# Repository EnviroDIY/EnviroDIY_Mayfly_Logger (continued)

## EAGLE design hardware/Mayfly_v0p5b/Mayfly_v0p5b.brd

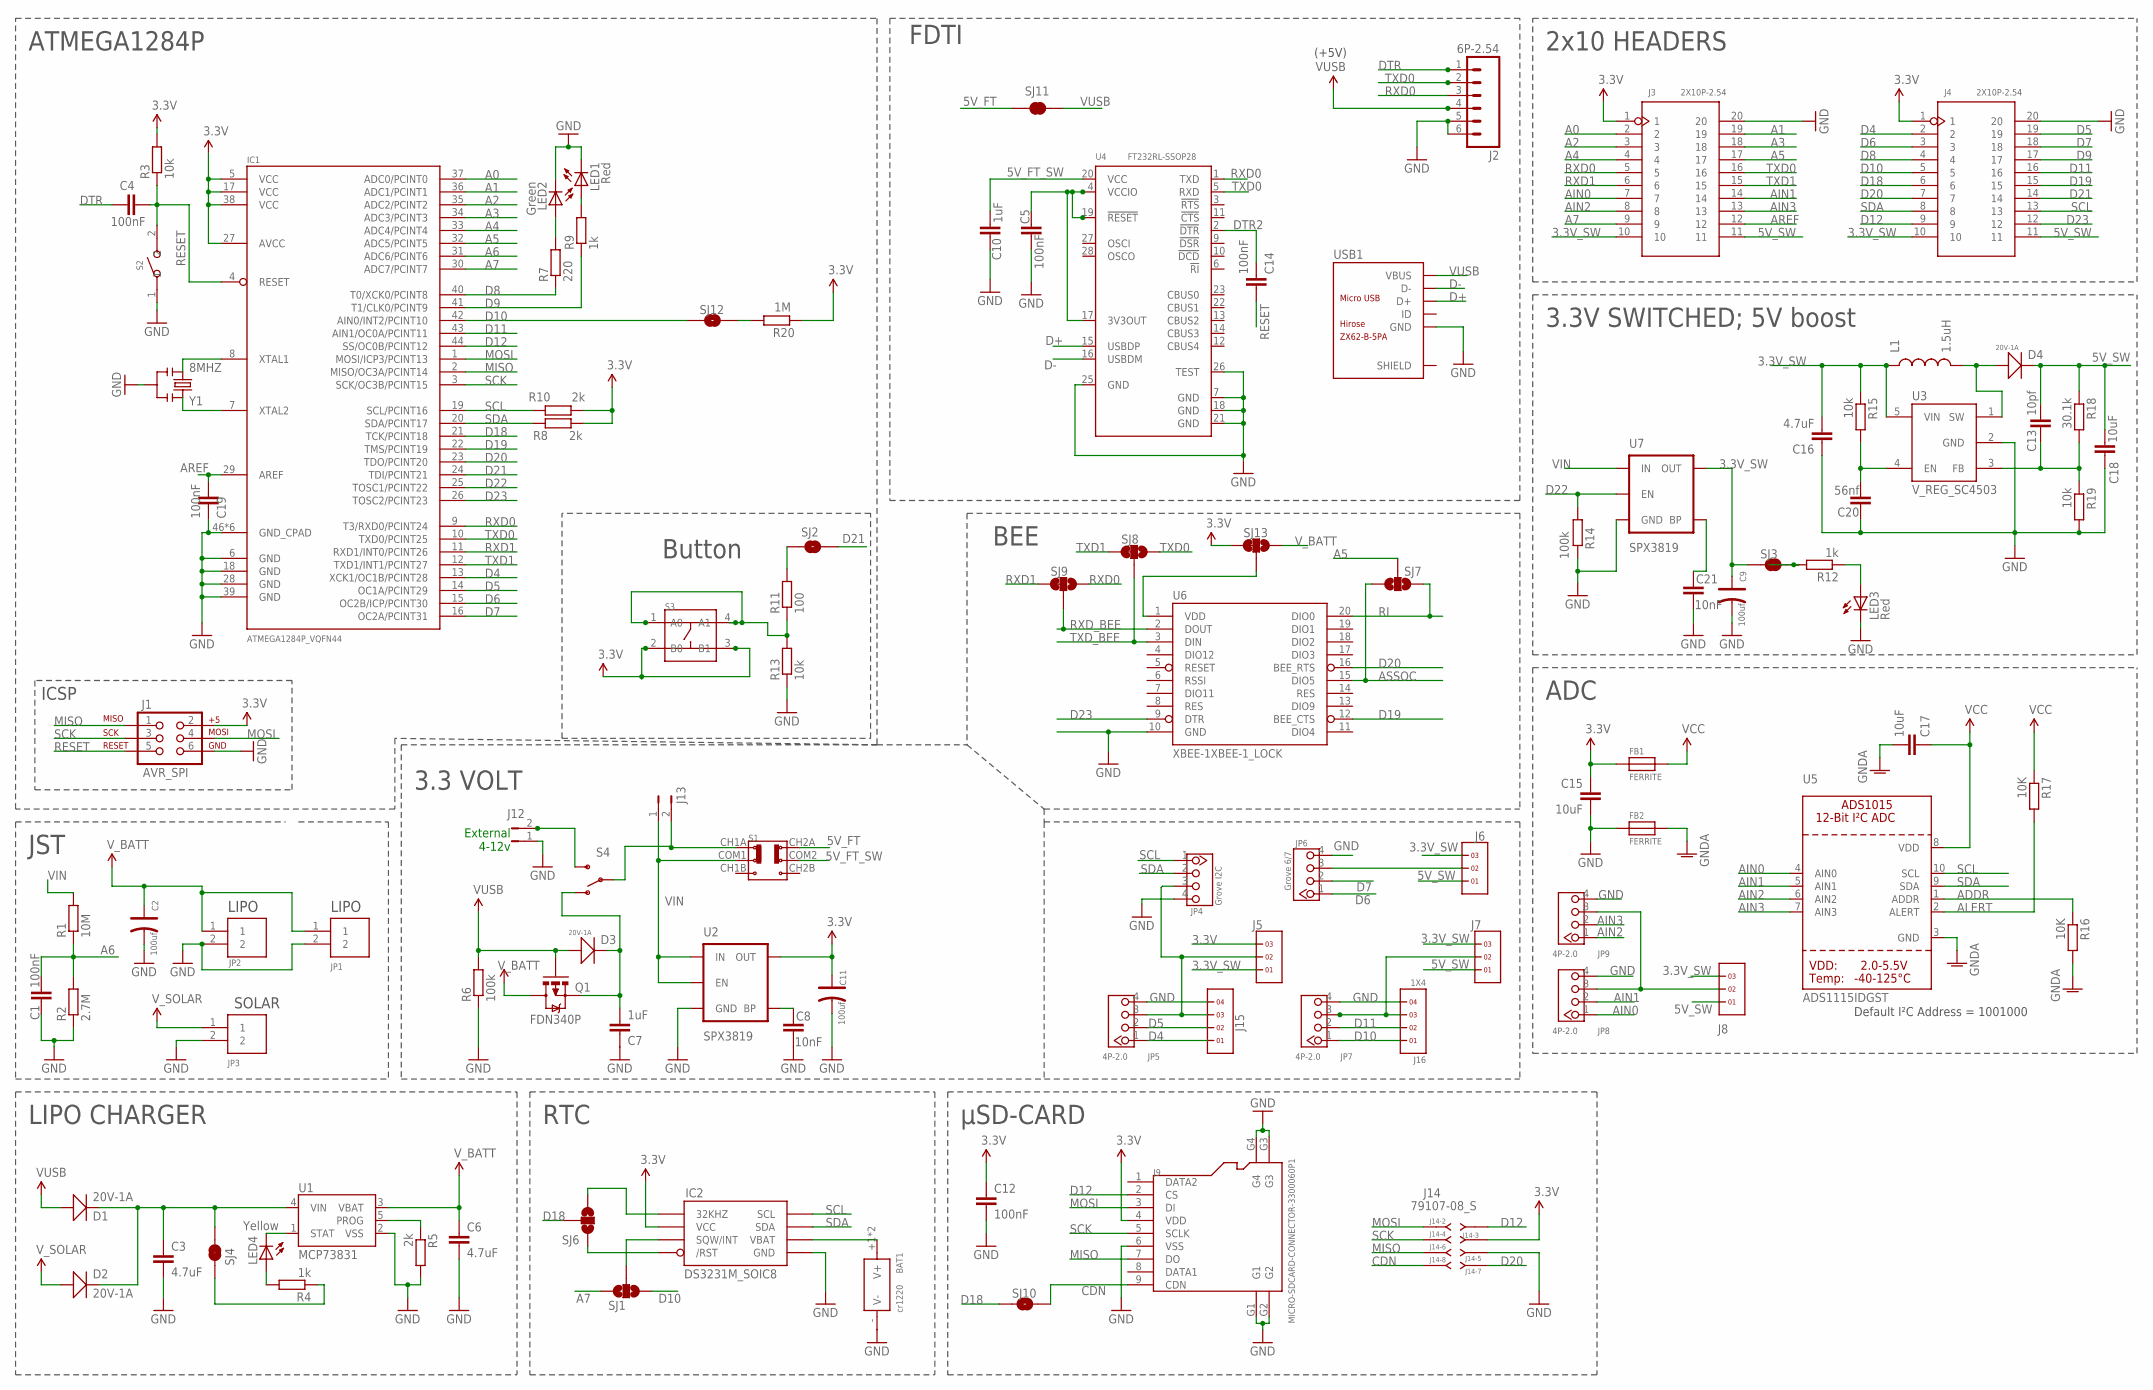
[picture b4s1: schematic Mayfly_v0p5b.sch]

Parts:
BAT1: cr1220; BAT2P-13.5-CR1220
C1, C4, C5, C12, C14, C19: 100nF; C0603
C2, C9, C11: 100uf; AVX-B
C3, C6: 4.7uF; C0603
C7, C10: 1uF; C0603
C8, C21: 10nF; C0603
C13: 10pf; 0603-CAP
C15, C17: 10uF; C0603
C16: 4.7uF; 0805
C18: 10uF; 0805
C20: 56nf; 0603-CAP
D1, D2, D3, D4: 20V-1A; SOD-123
FB1, FB2: FERRITE; 0805
IC1: ATMEGA1284P_VQFN44; VQFN44
IC2: DS3231M_SOIC8; SO8
J1: AVR_SPI; 2X3-NS
J2: 6P-2.54; 1X06_FEMALE_LOCK.010
J3, J4: 2X10P-2.54; H2X10-2.54
J5, J6, J7, J8: 1X3
J9: MICRO-SDCARD-CONNECTOR-3300060P1; 9P-SMD-W-RING
J12, J13: JUMPER-PTH-2-NO; PTH-JUMPER-2-NO_NO_SILK
J14: 79107-08_S; 79107-08
J15, J16: 1X4
JP1, JP2, JP3: JST_EPH_2PIN; JST_EPH_B2B-PH-K-S
JP4: Grove I2C; HW4-2.0
JP5, JP7, JP8, JP9: 4P-2.0; HW4-2.0
JP6: Grove 6/7; HW4-2.0
L1: 1.5uH; VLF4012A
LED1, LED3: Red; LED-0603
LED2: Green; LED-0603
LED4: Yellow; LED-0603
Q1: FDN340P; SOT23-S-PADS
R1: 10M; R0603
R2: 2.7M; R0603
R3, R13, R15, R19: 10k; R0603
R4, R9, R12: 1k; R0603
R5, R8, R10: 2k; R0603
R6, R14: 100k; R0603
R7: 220; R0603
R11: 100; R0603
R16, R17: 10K; R0603
R18: 30.1k; R0603
R20: 1M; R0603
S1: SWITCH-2CH-6P-3010010P1; 6P-2CH-2.54-9.1X3.5X3.2+2H
S2: SMD-BUTTON(2P-6.0X3.0X2.5MM)-DHT-1163S; SW2-4.0-6.0X3.0X2.5MM
S3: SMD-SWITCH-TACTILE-SPST-NO(4P-D6.0MM); SW4-SMD-6.0X6.0X5.0MM
S4: SWITCH-SPDT-SMD-A; SWITCH-SPST-SMD-A
SJ1, SJ6, SJ7: SOLDERJUMPER_2WAYT; SJ_2
SJ2, SJ3, SJ10, SJ12: SOLDERJUMPERNO; SJ_2S-NO
SJ4: SOLDERJUMPER_NC; SJ_2S_NC
SJ8, SJ9, SJ13: SJ_3WAY_12SHORT
SJ11: JUMPER-PAD-2-NC_BY_TRACENO_SILK; PAD-JUMPER-2-NC_BY_TRACE_NO_SILK
U1: MCP73831; SOT23-5
U2, U7: SPX3819; SOT23-5
U3: V_REG_SC4503; SOT23-5
U4: FT232RL-SSOP28; SSOP28-0.65-10.2X5.2MM
U5: ADS1115IDGST; MSOP10
U6: XBEE-1XBEE-1_LOCK; XBEE-1_LOCK
USB1: ZX62-B-5PA; MICRO-USB5+6P-SMD-0.65-AB
Y1: 8MHZ; X3-SMD-3.6X1.3X0.8MM

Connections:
1.8V: D2.+, JP3.1
3.3V: C11.+, C12.2, C15.1, FB1.1, IC1.5 (VCC), IC1.17 (VCC), IC1.27 (AVCC), IC1.38 (VCC), IC2.2 (VCC), J1.2, J3.1, J4.1, J5.3, J9.4 (VDD), J14.3, R3.2, R8.1, R10.2, R20.2, S3.2 (B0), S3.3 (B1), SJ13.1, U2.5 (OUT)
3.3V_SW: C9.+, C16.2, J3.10, J4.10, J5.1, J6.3, J7.3, J8.3, L1.P$1 (1), R15.1, SJ3.1, U3.5 (VIN), U7.5 (OUT)
5V_FT: S1.CH2A, SJ11.1
5V_FT_SW: C10.2, S1.COM2, U4.20 (VCC)
5V_SW: C13.2, C18.1, D4.-, J3.11, J4.11, J6.1, J7.1, J8.1, R18.1
A0: IC1.37 (ADC0/PCINT0), J3.2
A1: IC1.36 (ADC1/PCINT1), J3.19
A2: IC1.35 (ADC2/PCINT2), J3.3
A3: IC1.34 (ADC3/PCINT3), J3.18
A4: IC1.33 (ADC4/PCINT4), J3.4
A5: IC1.32 (ADC5/PCINT5), J3.17, SJ7.2
A6: C1.2, IC1.31 (ADC6/PCINT6), R1.1, R2.2
A7: IC1.30 (ADC7/PCINT7), J3.9, SJ1.3
ADDR: R16.1, U5.1 (ADDR)
AIN0: J3.7, JP8.1, U5.4 (AIN0)
AIN1: J3.14, JP8.2, U5.5 (AIN1)
AIN2: J3.8, JP9.1, U5.6 (AIN2)
AIN3: J3.13, JP9.2, U5.7 (AIN3)
ALERT: R17.2, U5.2 (ALERT)
AREF: C19.2, IC1.29 (AREF), J3.12
ASSOC: SJ7.3, U6.15 (DIO5)
C: IC1.8 (XTAL1), Y1.1
CDN: J9.9 (CDN), J14.8, SJ10.2
C_N: IC1.7 (XTAL2), Y1.3
D4: IC1.13 (XCK1/OC1B/PCINT28), J4.2, J15.1, JP5.1
D5: IC1.14 (OC1A/PCINT29), J4.19, J15.2, JP5.2
D6: IC1.15 (OC2B/ICP/PCINT30), J4.3, JP6.1
D7: IC1.16 (OC2A/PCINT31), J4.18, JP6.2
D8: IC1.40 (T0/XCK0/PCINT8), J4.4, R7.1
D9: IC1.41 (T1/CLK0/PCINT9), J4.17, R9.1
D10: IC1.42 (AIN0/INT2/PCINT10), J4.5, J16.1, JP7.1, SJ1.1, SJ12.1
D11: IC1.43 (AIN1/OC0A/PCINT11), J4.16, J16.2, JP7.2
D12: IC1.44 (SS/OC0B/PCINT12), J4.9, J9.2 (CS), J14.1
D18: IC1.21 (TCK/PCINT18), J4.6, SJ6.2, SJ10.1
D19: IC1.22 (TMS/PCINT19), J4.15, U6.12 (BEE_CTS)
D20: IC1.23 (TDO/PCINT20), J4.7, J14.7, U6.16 (BEE_RTS)
D21: IC1.24 (TDI/PCINT21), J4.14, SJ2.2
D22: IC1.25 (TOSC1/PCINT22), R14.2, U7.3 (EN)
D23: IC1.26 (TOSC2/PCINT23), J4.12, U6.9 (DTR)
D+: U4.15 (USBDP), USB1.3 (D+)
D-: U4.16 (USBDM), USB1.2 (D-)
DTR: C4.1, J2.1
DTR2: C14.2, U4.2 (!DTR)
GND: BAT1.- (V-), C1.1, C2.-, C3.2, C5.1, C6.2, C7.1, C8.1, C9.-, C10.1, C11.-, C12.1, C15.2, C16.1, C18.2, C19.1, C20.1, C21.1, FB2.1, IC1.6 (GND), IC1.18 (GND), IC1.28 (GND), IC1.39 (GND), IC1.46 (GND_CPAD), IC1.GND@0 (GND_CPAD), IC1.GND@1 (GND_CPAD), IC1.GND@2 (GND_CPAD), IC1.GND@3 (GND_CPAD), IC1.GND@4 (GND_CPAD), IC2.5 (GND), J1.6, J2.5, J2.6, J3.20, J4.20, J9.6 (VSS), J9.G1, J9.G2, J9.G3, J9.G4, J12.1, J14.5, J15.4, J16.4, JP1.2, JP2.2, JP3.2, JP4.4, JP5.4, JP6.4, JP7.4, JP8.4, JP9.4, LED1.C, LED2.C, LED3.C, R2.1, R5.2, R6.1, R13.1, R14.1, R19.2, S2.1, U1.2 (VSS), U2.2 (GND), U3.2 (GND), U4.7 (GND), U4.18 (GND), U4.21 (GND), U4.25 (GND), U4.26 (TEST), U6.10 (GND), U7.2 (GND), USB1.5 (GND), Y1.2
GNDA: C17.2, FB2.2, R16.2, U5.3 (GND)
LIPO_STAT: LED4.C, U1.1 (STAT)
MISO: IC1.2 (MISO/OC3A/PCINT14), J1.1, J9.7 (DO), J14.6
MOSI: IC1.1 (MOSI/ICP3/PCINT13), J1.4, J9.3 (DI), J14.2
unnamed: R20.1, SJ12.2
unnamed: C8.2, U2.4 (BP)
unnamed: R12.2, SJ3.2
unnamed: LED3.A, R12.1
unnamed: R11.1, R13.2, S3.1 (A0), S3.4 (A1)
unnamed: J8.2, JP8.3, JP9.3
unnamed: C5.2, U4.4 (VCCIO), U4.17 (3V3OUT), U4.19 (!RESET)
unnamed: D4.+, L1.P$2 (2), U3.1 (SW)
unnamed: SJ13.2, U6.1 (VDD)
unnamed: IC2.3 (SQW/INT), SJ1.2
unnamed: C7.2, D3.-, Q1.2 (S), S4.1 (O)
unnamed: LED4.A, R4.2
unnamed: R5.1, U1.5 (PROG)
unnamed: C3.1, D1.-, D2.-, SJ4.2, U1.4 (VIN)
unnamed: R4.1, SJ4.1
unnamed: J5.2, J15.3, JP4.3, JP5.3
unnamed: R11.2, SJ2.1
unnamed: J6.2, JP6.3
unnamed: J12.2, S4.3 (S)
unnamed: C21.2, U7.4 (BP)
unnamed: C13.1, R18.2, R19.1, U3.3 (FB)
unnamed: J7.2, J16.3, JP7.3
unnamed: J13.2, S1.CH1A, S4.2
unnamed: C20.2, R15.2, U3.4 (EN)
unnamed: LED1.A, R9.2
unnamed: BAT1.+1 (V+), BAT1.+2 (V+), IC2.6 (VBAT)
unnamed: LED2.A, R7.2
RESET: C4.2, C14.1, IC1.4 (RESET), J1.5, R3.1, S2.2
RI: SJ7.1, U6.20 (DIO0)
RTC_32KHZ: IC2.1 (32KHZ), SJ6.1
RTC_RST: IC2.4 (/RST), SJ6.3
RXD0: IC1.9 (T3/RXD0/PCINT24), J2.3, J3.5, SJ9.3, U4.1 (TXD)
RXD1: IC1.11 (RXD1/INT0/PCINT26), J3.6, SJ9.1
RXD_BEE: SJ9.2, U6.2 (DOUT)
SCK: IC1.3 (SCK/OC3B/PCINT15), J1.3, J9.5 (SCLK), J14.4
SCL: IC1.19 (SCL/PCINT16), IC2.8 (SCL), J4.13, JP4.1, R10.1, U5.10 (SCL)
SDA: IC1.20 (SDA/PCINT17), IC2.7 (SDA), J4.8, JP4.2, R8.2, U5.9 (SDA)
TXD0: IC1.10 (TXD0/PCINT25), J2.2, J3.16, SJ8.3, U4.5 (RXD)
TXD1: IC1.12 (TXD1/INT1/PCINT27), J3.15, SJ8.1
TXD_BEE: SJ8.2, U6.3 (DIN)
VCC: C17.1, FB1.2, R17.1, U5.8 (VDD)
VIN: J13.1, R1.2, S1.COM1, U2.1 (IN), U2.3 (EN), U7.1 (IN)
VUSB: D1.+, D3.+, J2.4, Q1.1 (G), R6.2, SJ11.2, USB1.1 (VBUS)
V_BATT: C2.+, C6.1, JP1.1, JP2.1, Q1.3 (D), SJ13.3, U1.3 (VBAT)

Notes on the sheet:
ATMEGA1284P
BEE
JST
RTC
SOLAR
LIPO
LIPO CHARGER
3.3 VOLT
(+5V)
FDTI
µSD-CARD
ICSP
ADC
Default I²C Address = 1001000
2x10 HEADERS
3.3V SWITCHED; 5V boost
Button
External 4-12v

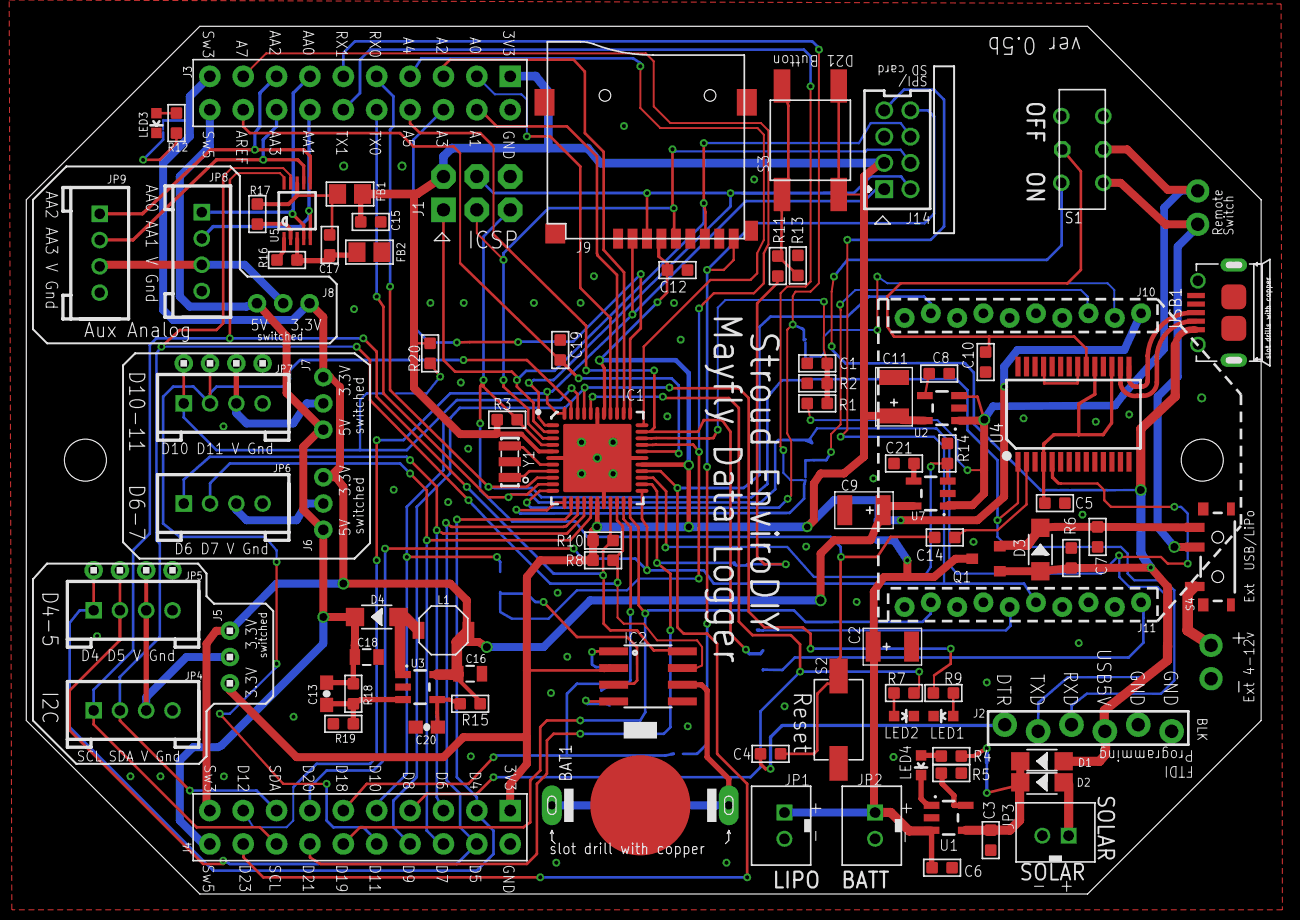
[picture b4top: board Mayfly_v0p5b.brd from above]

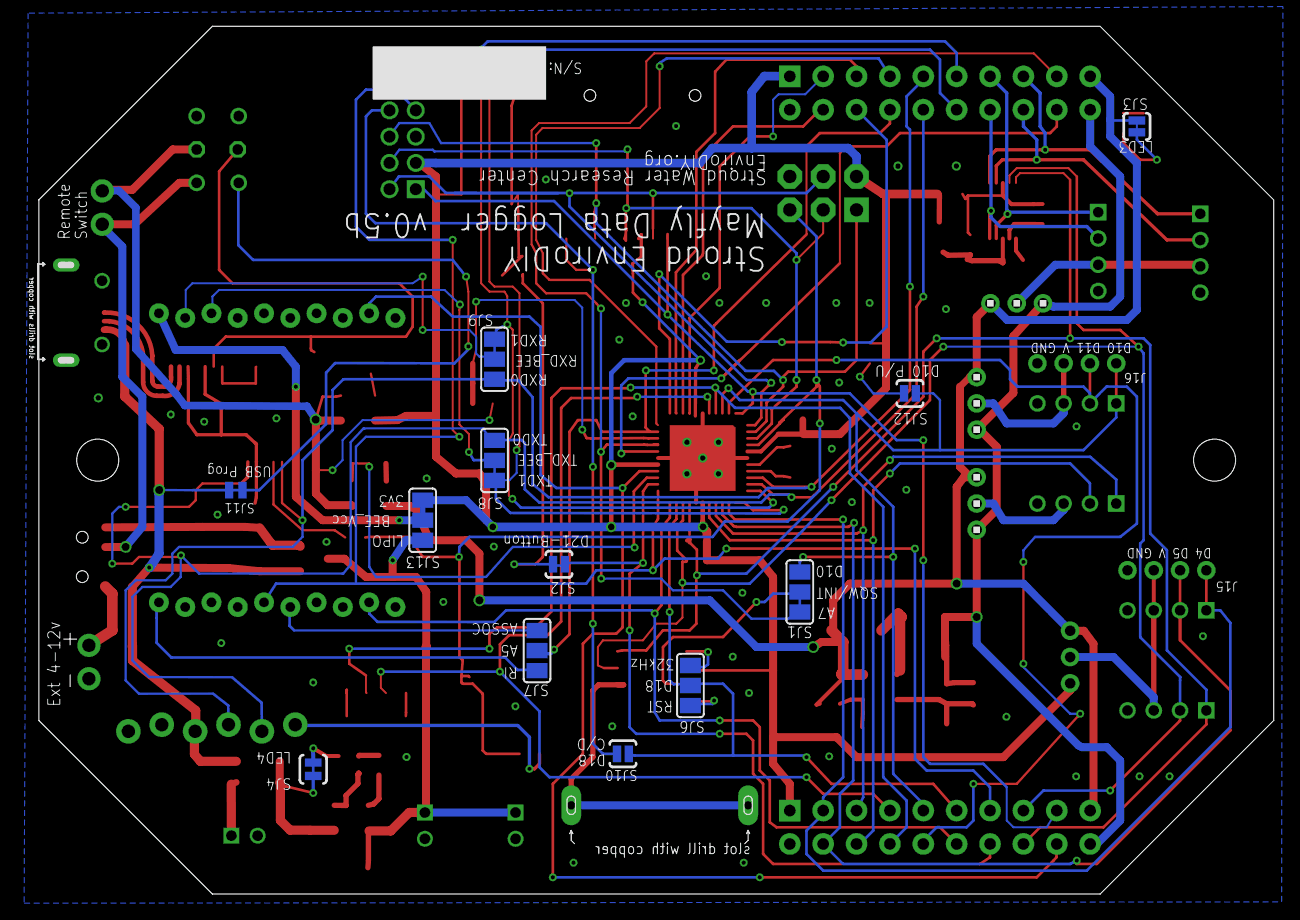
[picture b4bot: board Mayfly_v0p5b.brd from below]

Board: 4 copper layers, 94.0 x 66.0 mm, 104 parts (15 on the bottom side), 93 nets.

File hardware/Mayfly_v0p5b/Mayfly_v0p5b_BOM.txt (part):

Partlist exported from /Users/fisher/Downloads/Mayfly_v0p5b/Mayfly_v0p5b.sch at 6/5/19 5:30 PM

Part Value                            Device                                     Package                          Description                                                                             MPN                PROD_ID  VALUE         
BAT1 cr1220                           DIP-BATTERY-CELL-HOLDER(1220)              BAT2P-13.5-CR1220                320170002                                                                                                           cr1220        
C1   100nF                            C_0603                                     C0603                                                                                                                                                              
C2   100uf                            TANTALUM-SMD-100UF-10V(AVX-B)              AVX-B                            302020015                                                                               TAJB107M010#NJ              100uf         
C3   4.7uF                            C_0603                                     C0603                                                                                                                                                              
C4   100nF                            C_0603                                     C0603                                                                                                                                                              
C5   100nF                            C_0603                                     C0603                                                                                                                                                              
C6   4.7uF                            C_0603                                     C0603                                                                                                                                                              
C7   1uF                              C_0603                                     C0603                                                                                                                                                              
C8   10nF                             C_0603                                     C0603                                                                                                                                                              
C9   100uf                            TANTALUM-SMD-100UF-10V(AVX-B)              AVX-B                            302020015                                                                               TAJB107M010#NJ              100uf         
C10  1uF                              C_0603                                     C0603                                                                                                                                                              
C11  100uf                            TANTALUM-SMD-100UF-10V(AVX-B)              AVX-B                            302020015                                                                               TAJB107M010#NJ              100uf         
C12  100nF                            C_0603                                     C0603                                                                                                                                                              
C13  10pf                             CAP0603-CAP                                0603-CAP                         Capacitor                                                                                                                         
C14  100nF                            C_0603                                     C0603                                                                                                                                                              
C15  10uF                             C_0603                                     C0603                                                                                                                                                              
C16  4.7uF                            CAP0805                                    0805                             Capacitor                                                                                                                         
C17  10uF                             C_0603                                     C0603                                                                                                                                                              
C18  10uF                             CAP0805                                    0805                             Capacitor                                                                                                                         
C19  100nF                            C_0603                                     C0603                                                                                                                                                              
C20  56nf                             CAP0603-CAP                                0603-CAP                         Capacitor                                                                                                                         
C21  10nF                             C_0603                                     C0603                                                                                                                                                              
D1   20V-1A                           SMD-DIODE-SCHOTTKY-20V-1A(SOD-123)         SOD-123                          304020034                                                                               B5819W                      20V-1A        
D2   20V-1A                           SMD-DIODE-SCHOTTKY-20V-1A(SOD-123)         SOD-123                          304020034                                                                               B5819W                      20V-1A        
D3   20V-1A                           SMD-DIODE-SCHOTTKY-20V-1A(SOD-123)         SOD-123                          304020034                                                                               B5819W                      20V-1A        
D4   20V-1A                           SMD-DIODE-SCHOTTKY-20V-1A(SOD-123)         SOD-123                          304020034                                                                               B5819W                      20V-1A        
FB1  FERRITE                          FERRITE0805                                0805                             Ferrite Bead                                                                                                                      
FB2  FERRITE                          FERRITE0805                                0805                             Ferrite Bead                                                                                                                      
IC1  ATMEGA1284P_VQFN44               ATMEGA1284P_VQFN44                         VQFN44                                                                                                                                                             
IC2  DS3231M_SOIC8                    DS3231M_SOIC8                              SO8                                                                                                                                                                
J1   AVR_SPI                          AVR_SPI_PRG_6NS                            2X3-NS                           AVR ISP 6 Pin                                                                                                                     
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
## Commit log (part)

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2016-07-20 :boom::camel: Added .gitattributes & .gitignore files
2016-07-21 Adding workshop sketches
2016-07-21 Initial Readme file
    to copy in all other directories
2016-07-21 Adding Readme
2016-07-22 Create content for Readme files
    At root and for basic doc.
2016-07-22 Scaled image in Readme
2016-07-22 Expanded "Getting Started" on Readme
    in root
2016-07-22 Added sonar sensor examples
2016-07-22 Update filename
2016-07-23 Renaming files
2016-07-23 Adding examples
2016-07-27 Added NSF awards to credits in root ReadMe
2016-07-27 Added comments to workshop sketches
    Also changed iterator in 01_blink from i++ to i=i+1, to slowly
    introduce such concepts.
2016-11-10 Modular code example - initial commit
2016-12-08 Condensed script to a single file, updated POST requests to use newest format and address
2017-01-08 Updated ReadMe in \Examples
2017-01-08 Edits to Examples directory
    * added initial_demo_blink_temperature sketch, from
    http://envirodiy.org/mayfly/software/, so that people could reproduce
    if they overwrite it.
    * Updated ReadMe to reflect above
    * removed “_1” from “blinking_LEDs” sketch name, to match EnviroDIY
    website.
2017-01-08 Added documentation to initial_demo_blink_temperature
2017-01-09 Added blink demo 2
    And renamed blink demo 1
2017-01-09 Beginning work on program to sync Mayfly with PC clock.
2017-01-11 Got the python program working!
    Note that the batch doesn't work.
2017-01-12 Added instructions, documentation, and requirements files. Removed the non-working batch file.
2017-01-12 Made check for Mayfly less restrictive and added step to verify that expected data is being sent from Mayfly.
2017-01-19 Removed extraneous bat file
2017-01-19 Added example, fixed variable name for onboard temp
2017-01-19 Added work so far on Decagon CTD
2017-01-23 Update gitignore.
2017-01-23 update gitignore
2017-01-24 Rearranged files slightly
2017-01-24 Changes to make for sara's desk
2017-01-24 Added modified XBee WiFi example
2017-01-25 First commit for example to push data to PC
2017-01-25 Added travix
2017-01-25 Messing with travis
2017-01-25 Correct Travis paths
2017-01-25 Still trying to get Travis to work
2017-01-25 come on, Travis..
2017-01-25 Travis...
2017-01-26 Moved in the sync_clock_pc folder
2017-01-26 working on travis..
2017-01-26 Still trying to get Travis to work..
2017-01-27 Adding pio update to Travis.
2017-01-31 Does send data to serial port.. not optimized.
2017-02-02 Modified to make executable from python, add config file
2017-02-02 Add platformio config file
2017-02-02 changed serial baud rate, prints sketch name
2017-02-02 rearranged program to please linter.
2017-02-02 Made more generic, added exceptions, fixed exe
    Made the python in ino scripts more generic so they reference any FTDI
    device instead of the Mayfly. Also added more places to catch
    exceptions in the python script. Hopefully this will prevent the exe
    from just flashing open and closing again for people.
2017-02-03 Removed the clock sync
    Removed the clock sync example. That has now been pushed to the
    EnviroDIY fork of the DS3231 library.
2017-02-03 Early draft of mayfly_temp_gprs6_portal_example.ino
    Not complete or tested
2017-02-03 Add ReadMe to Workshop/mayfly_01_blink
2017-02-03 Updat docs for Workshop/mayfly_05_blink_temperature.ino
2017-02-03 Fixed various typos & added comments
2017-02-03 Removed empty archive folder
2017-02-03 Add documentation to workshop sketches
    Sketches 1, 2, 6
2017-02-03 Updated Travis and pio configs to stop failing
2017-02-03 Now: #include <wire.h>. Sorry PIO!
2017-02-03 Wire, not wire.
2017-02-05 Got simple_logging_example working
    Got the simple_logging_example working using Shannon's timer functions.
    Also fixed the usu script to not always print success. Removed the
    broken "logging_to_pc" script. Also removed the sync_clock_pc because
    that is now an example in the Sodaq library.
2017-02-05 Many failed attempts to make requests
2017-02-06 Updated Workshop 6 DHT docs
    To update documentation on the Adafruit library and to include docs on
    the Grove port power pin (22).
    Also mayfly_08_magnetswitch.ino
    Need to update all other Grove sketches with these comments.
2017-02-06 Functions but still seems to send and recieve junk
2017-02-07 Created load test, deleted bad tests
2017-02-07 Moved to logging_to_enviroDIY
    Renamed the simple_logging_example to logging_to_EnviroDIY, which I
    think is more descriptive. Also created a ReadMe and improved the
    WiFiBee instructions.
2017-02-07 Removed library files, moved xbee config
2017-02-07 Removed extra profiles
2017-02-07 Fixed Travis for renames
2017-02-07 Sorry Travis
    I think half of my commits are because I screwed up something for
    Travis..
2017-02-07 PIO submod trouble
2017-02-07 Added TravisCI
2017-02-07 Created load test
2017-02-07 Removed library files, moved xbee config Removed extra profiles Fixed Travis for renames
2017-02-07 Updated gitignore
2017-02-07 Ready for merge
2017-02-07 Readded doc and hardware
2017-02-07 Removed load test
    should not have been part of the examples, was just for internal testing
2017-02-07 Also removed unready example
2017-02-07 Removed bad reference to unused library
2017-02-08 Created a load test for the gprs
2017-02-08 Re-added deleted files to smooth merges.
2017-02-08 Fixed timestamp to ISO8601
2017-02-09 Edits to ReadMe.md to improve rendering
    The lists were rendering as code blocks, because of the 3 tab
    indentation. Reduced to two tabs.
2017-02-09 Improved ReadMe formatting
2017-02-09 Fixed broken link
2017-02-10 Aligned GPRS and Wifi Load Examples
2017-02-10 Increased size of load tests.
2017-02-10 Tweaked WiFi load to not keep string in memory
2017-02-10 Tweaked WiFi to not store string in memory
2017-02-13 Update documentation on Example:Battery
    examples/battery_measurement.ino
2017-02-14 Added memory tests, begin to try char instead
2017-02-14 F() strings
2017-02-14 Condensed functions to stream
2017-02-14 Fixed load fxns in GPRS
2017-02-14 Consolidated load tests
2017-02-14 Applied memory improvements to example
2017-02-14 Applied memory improvements
2017-02-15 Update docs & typos to "logging_to_EnviroDIY.ino"
    Full read-through of code and ReadMe file, with minor edits to
    documentation and comments.
2017-02-15 Rearranged files
2017-02-16 Attemptiing multi-vars as array
2017-02-16 Totally not working
2017-02-17 It's working!!
2017-02-18 Renaming "mods"
2017-02-19 Added dreamhost to modular sensor sending
2017-02-20 modular sensors are working!
2017-02-23 Updated config, et al.
2017-02-24 Updated Workshop 2 ReadMe.
2017-03-01 Initial commit of mayfly_11_DT-LED branch
    LimnoTech team is trying to mod 10-sonar by replacing Maxbotix sonar
    with Waterproof DS18B20 Digital temperature sensor
2017-03-01 Works with Grove DHT 11 sensor
    We don’t have the resistor for the DS18B20 sensor (bummer)!
2017-03-06 Changed Travis config to cache library
2017-03-08 Renamed files; created 10c for DS18B20 temperature
    Now have workshop sketches: 10 (Maxbotix), 10b (DHT), 10c (DS18B20
    Digital temperature)
2017-03-27 removed outdated examples
2017-03-27 Fixed sonar examples
2017-06-07 comments for demo understanding
2017-06-07 included tutorial text for blink demo
2017-06-07 link to Adafruit tutorial
2017-06-07 note about serial monitor part of blink demo
2017-06-07 added sketch provenance
2017-06-07 corrected readout to include temperature
2017-06-08 Sketch for Luminosity to display on LED
2017-06-08 improved readability of demo for first-time users
2017-06-08 Added documentation for clarity for new users
2017-06-22 Fixed DHT_LED
    Was printing humidity twice.
2018-01-08 Added schematics for 3 main versions of boards
2018-01-08 Updated readme for repo and hardware
2018-01-08 Update main readme
2018-01-08 fixed blink demo to alternate red & green
2018-01-09 Updated luminosity sketch to use library with unified sensor driver
    Adafruit considers the other library (v1) to be obsolete
2018-01-09 Travis and gitignore updates
2018-01-12 Fixed missing comma
2018-01-12 update luminosity examples and Travis
2018-01-12 Fixed directories in Travis
2018-01-12 Another OLED fix
2018-02-09 Copying sketches
2018-02-09 Blink sketches.
2018-02-09 rearranging files
2018-02-12 Fixed server IP address
2018-02-14 Revised logger lessons
2018-02-14 typo
2018-02-14 typo corrected
2018-02-14 typo corrected to master
2018-04-11 Delete mayfly_v0p3p_schematic2.jpg
    replacing with updated version that corrects a mislabeled ADC
2018-04-11 Delete mayfly_v0p4p_schematic.png
    replacing with updated version that corrects a mislabeled ADC
2018-04-11 Delete mayfly_v0p5p_schematic.png
    replacing with updated version that corrects a mislabeled ADC
2018-04-11 Add files via upload
    Adding schematics of all versions of the Mayfly
2019-02-06 Update README.md
    Corrected URL link to the CERN Open Hardware License 1.2
2019-02-11 Update logging to envirodiy
2019-02-11 Change SD to SDFat, some whitespace changes
2019-02-11 Delete `/learning` sketches
    Because now redundant with sketches in https://github.com/EnviroDIY/LearnEnviroDIYcode
2019-02-12 Added arduino_boards submodule
2019-02-12 Removed learning from travis, minor example sync
2019-02-17 Major update to docs; preparing for 0.5b DOI
    Most of this content was copied from https://www.envirodiy.org/mayfly/.
    The purpose is to bundle this documenation with a future 0.5b release to Zenodo.
2019-02-17 Fixing links
    Seems like relative links only work in root ReadMe.md file.
2019-02-17 fix more links
2019-02-17 Minor docs cleanup
2019-02-18 Remove duplication in ReadMe files
    For v0.5b release!
2019-02-18 Update Intro_GettingStarted.md
    Fixed links
2019-04-24 Update Destination IP to LimnoTech
    The portal migrated from USU servers to LimnoTech servers, requiring a change to the static IP address of the Destination.
2019-04-25 Update xbee_radio_config.xml
    to match IP change with https://github.com/EnviroDIY/EnviroDIY_Mayfly_Logger/commit/82e0dfc683ac67af81396e2b462486c532a26620.
    Not sure if line 19 should also be changed.
2019-06-05 Exported Bill of Materials from Eagle
    I need to replace several fried RTCs and I am searching for the right part.
    DigiKey 8-footed DS3231 are DS3231MZ/V+-ND and DS3231MZ+-ND
    and it seems like either would work. @s-hicks2 or @bschulz1701, is the "/V" in the part number meaningful to you? Which one should I pick? My gut is the one not labeled as automotive.
    BOM says
    IC2 DS3231M_SOIC8 DS3231M_SOIC8 SO8
2019-12-11 Added links to Pelican drill template
    In ReadMe.md for Hardware.
2020-04-01 Add detail to battery voltage ReadMe
2020-04-01 Update travis
2020-04-01 Overhauled readme
2020-04-01 Add readme for blink v1
2020-04-01 Fix backward voltage level in text
2020-04-01 Update blink v2
2020-04-01 Correct LED colors
2020-04-01 Added other ReadMe's
2020-04-21 Update ReadMe.md
    corrected voltage divider ratio
2020-04-21 Delete equation2.png
    this is incorrect
2020-05-13 Update Readme.md
    I fixed a grammar error in one of the sentences so it makes more sense. fixed a spelling error. very minor stuff, but hope it helps. Thanks for the documentation.
2026-02-09 Rename hardware/Mayfly_v0p5b_BOM.txt to hardware/Mayfly_v0p5b/Mayfly_v0p5b_BOM.txt
2026-02-09 Rename hardware/mayfly_v0p5b_schematic.png to hardware/Mayfly_v0p5b/mayfly_v0p5b_schematic.png
2026-02-09 Rename hardware/1120Pelican_enviroDIY_5.pdf to hardware/Enclosures/1120Pelican_enviroDIY_5.pdf
2026-02-09 Rename hardware/mayfly_v0p3_schematic.png to hardware/Mayfly_v0p3/mayfly_v0p3_schematic.png
2026-02-09 Rename hardware/mayfly_v0p5_schematic.png to hardware/Mayfly_0p5/mayfly_v0p5_schematic.png
2026-02-09 Rename hardware/mayfly_v0p4_schematic.png to hardware/Mayfly_0p4/mayfly_v0p4_schematic.png
2026-02-09 Rename Hardware_BoardFeatures.md to Hardware_BoardFeatures_v0p5.md
2026-02-09 Rename Hardware_JumperSettings.md to Hardware_JumperSettings_v0p5.md
2026-02-09 Rename 1p0_revA3_public.png to Mayfly_v1p0_revA3_public.png
2026-02-16 Rename mayfly_groveports.jpg to mayfly0.5_groveports.jpg
